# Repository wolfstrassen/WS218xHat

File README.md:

# WS218xHat
Hat for controlling WS218x leds using a RPi for a cleaner setup. This, altough is not technically a hat since it does not follow [raspberry hats guidelines](https://github.com/raspberrypi/hats "Rasbperry Hat guidelines"), but for all practicall purposes it is

This hat was made with the intention of make a Hyperion setup cleaner and easier by making all the wire splicing and connections directly on the board, reducing clutter behind your tv or near the LED strip connections.

##Features

- **Easy connection to the power supply:** This board includes a barrel jack that make an easy connection to an external power supply.
- **Voltage translator:** This board incorporates a voltaje translator from 3.3V to 5V on GPIO18 to aid with certain led strips that do not work well with 3.3V signaling, this can be bypass by soldering the JP2 jumper behind the board and not placing R1, R2 and Q1, but I strongly recommend to solder these components for better compatibility
- **Direct power from the 40-pin connector:** This board has the capability of powering the RPi board directly from the 40-pin connector by soldering JP1, but its important to note that **you only should do this if your power supply is within USB specs** because this voltaje will also reflects on your USB devices. In my case my power supply provided 5.3V and was out of spec (5.25V is the max allowed by these specifications) so I had to power the Raspberry from the USB connector on the board.
- **Power from USB connector on the board:** This usb connector on the board takes the power from the barrel jack and enables to powering the RPi from a short usb cable. Powering from the usb cable has certain advantages like a fuse and voltage regulators that drop down the 5.3V from my power supply to 5.1V, making it safe for the usb devices connected to the Raspberry pi
- **Easy connection to LEDs strips**: Most led strips came with a wire that you can plug easily to a terminal block. I just had to extend this enough to put the electronics in the cabinet instead of the back of my TV and connect the 3 wires to the terminal block on the board. Since the ammount of current that flows trough the LED strip is quite high, it is recommended to connect both the begining and end of the 5V and GND lines to the terminal block to reduce voltage drop

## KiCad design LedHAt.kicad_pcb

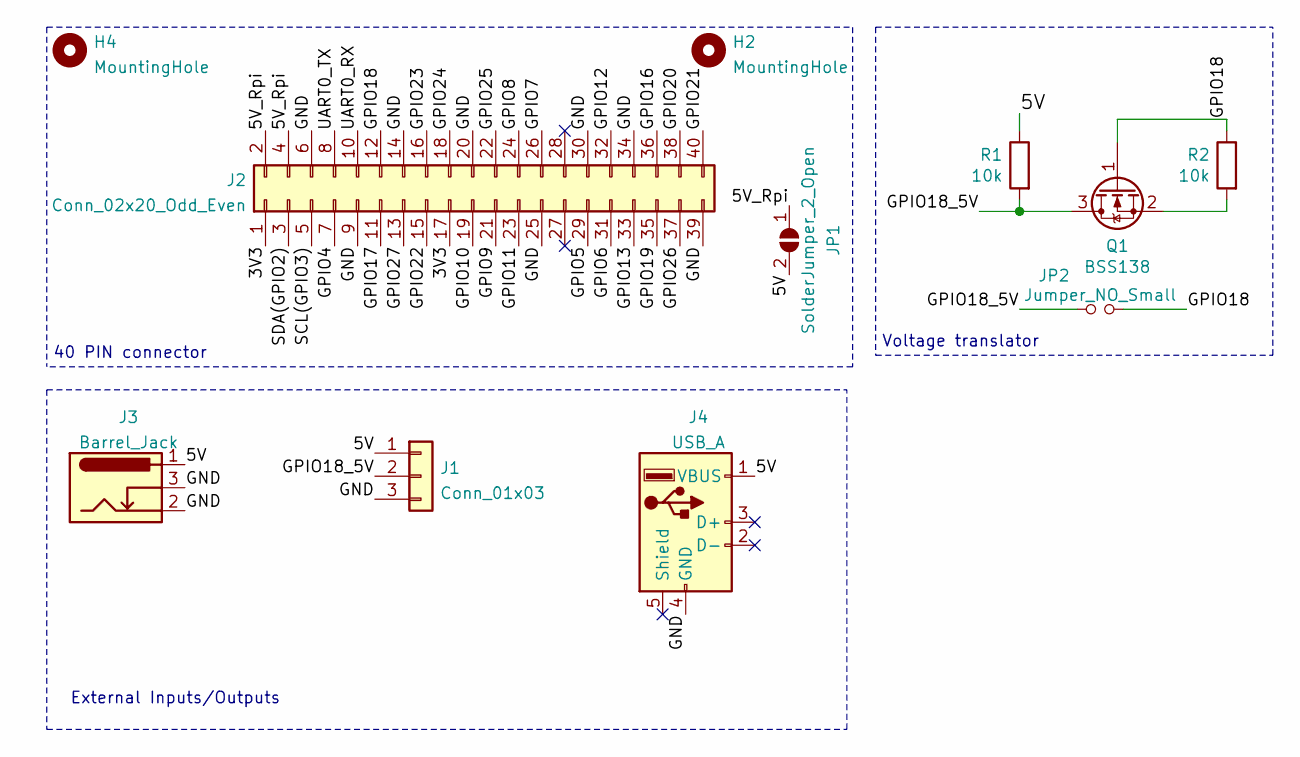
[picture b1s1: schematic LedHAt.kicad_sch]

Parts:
H2, H4: MountingHole; MountingHole_2.5mm
J1: Conn_01x03; TerminalBlock_Phoenix_MKDS-1,5-3_1x03_P5.00mm_Horizontal
J2: Conn_02x20_Odd_Even; PinSocket_2x20_P2.54mm_Vertical; MPN SSW-120-01-T-D
J3: Barrel_Jack; BarrelJack_Horizontal; MPN FC681465
J4: USB_A; USB_A_Molex_67643_Horizontal; MPN 67643
JP1: SolderJumper_2_Open; SolderJumper-2_P1.3mm_Open_Pad1.0x1.5mm
JP2: Jumper_NO_Small; SolderJumper-2_P1.3mm_Open_Pad1.0x1.5mm
Q1: BSS138; SOT-23; MPN BSS138
R1, R2: 10k; R_0603_1608Metric; MPN CR0603-JW-103ELF

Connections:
/3V3: J2.1, J2.17
/5V: J1.1, J3.1, J4.1 (VBUS), JP1.2 (B), R1.1
/5V_Rpi: J2.2, J2.4, JP1.1 (A)
/GND: J1.3, J2.6, J2.9, J2.14, J2.20, J2.25, J2.30, J2.34, J2.39, J3.2, J3.3, J4.4 (GND)
/GPIO4: J2.7
/GPIO5: J2.29
/GPIO6: J2.31
/GPIO7: J2.26
/GPIO8: J2.24
/GPIO9: J2.21
/GPIO10: J2.19
/GPIO11: J2.23
/GPIO12: J2.32
/GPIO13: J2.33
/GPIO16: J2.36
/GPIO17: J2.11
/GPIO18: J2.12, JP2.2, Q1.1 (G), R2.1
/GPIO18_5V: J1.2, JP2.1, Q1.3 (D), R1.2
/GPIO19: J2.35
/GPIO20: J2.38
/GPIO21: J2.40
/GPIO22: J2.15
/GPIO23: J2.16
/GPIO24: J2.18
/GPIO25: J2.22
/GPIO26: J2.37
/GPIO27: J2.13
/SCL(GPIO3): J2.5
/SDA(GPIO2): J2.3
/UART0_RX: J2.10
/UART0_TX: J2.8
unnamed: Q1.2 (S), R2.2

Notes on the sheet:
40 PIN connector
External Inputs/Outputs
Voltage translator

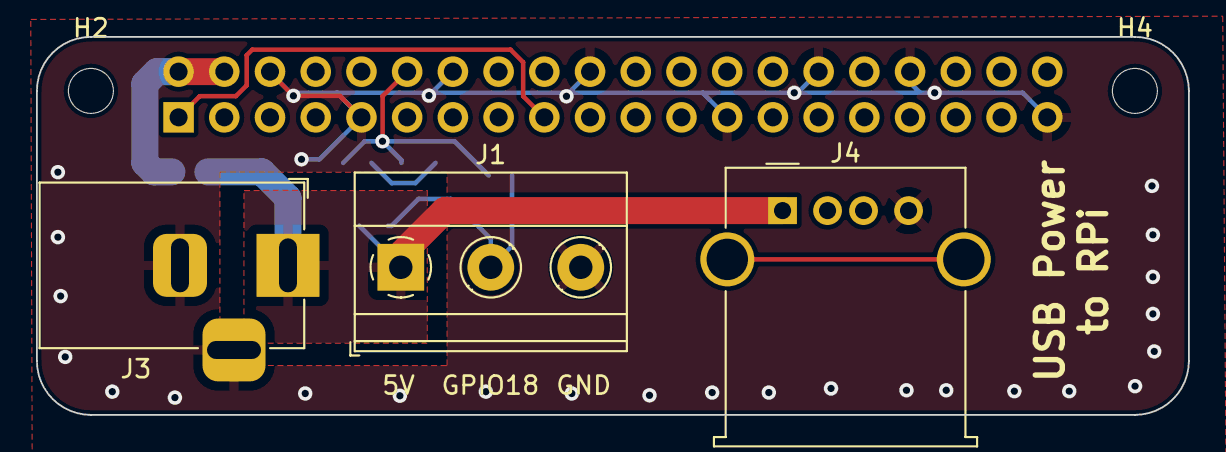
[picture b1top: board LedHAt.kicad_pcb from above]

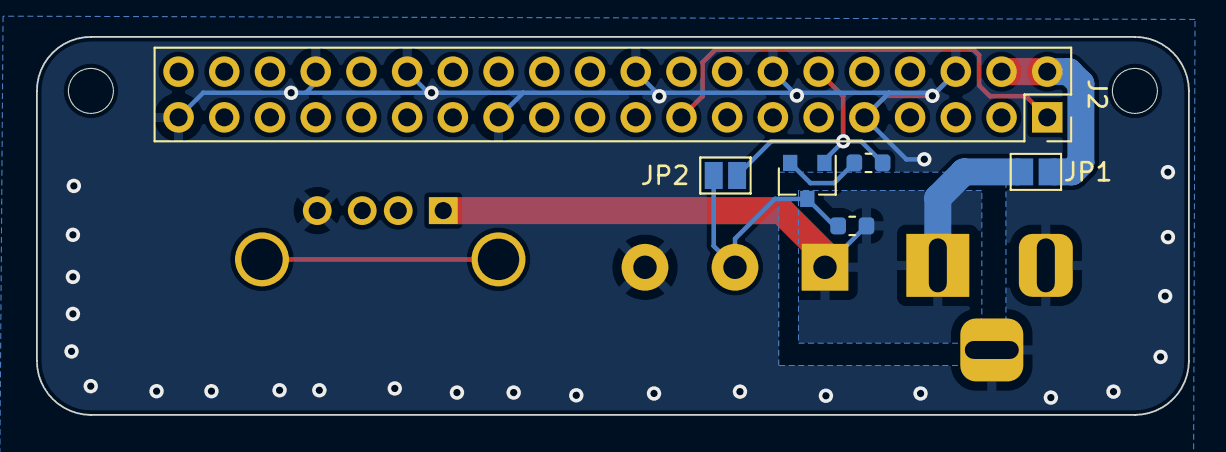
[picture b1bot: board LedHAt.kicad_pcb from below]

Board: 2 copper layers, 64.0 x 21.0 mm, 11 parts (6 on the bottom side), 7 nets.

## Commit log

2021-09-18 Added bill of materials
2021-09-18 feat: Updated readme
2021-09-18 feat: updated description
